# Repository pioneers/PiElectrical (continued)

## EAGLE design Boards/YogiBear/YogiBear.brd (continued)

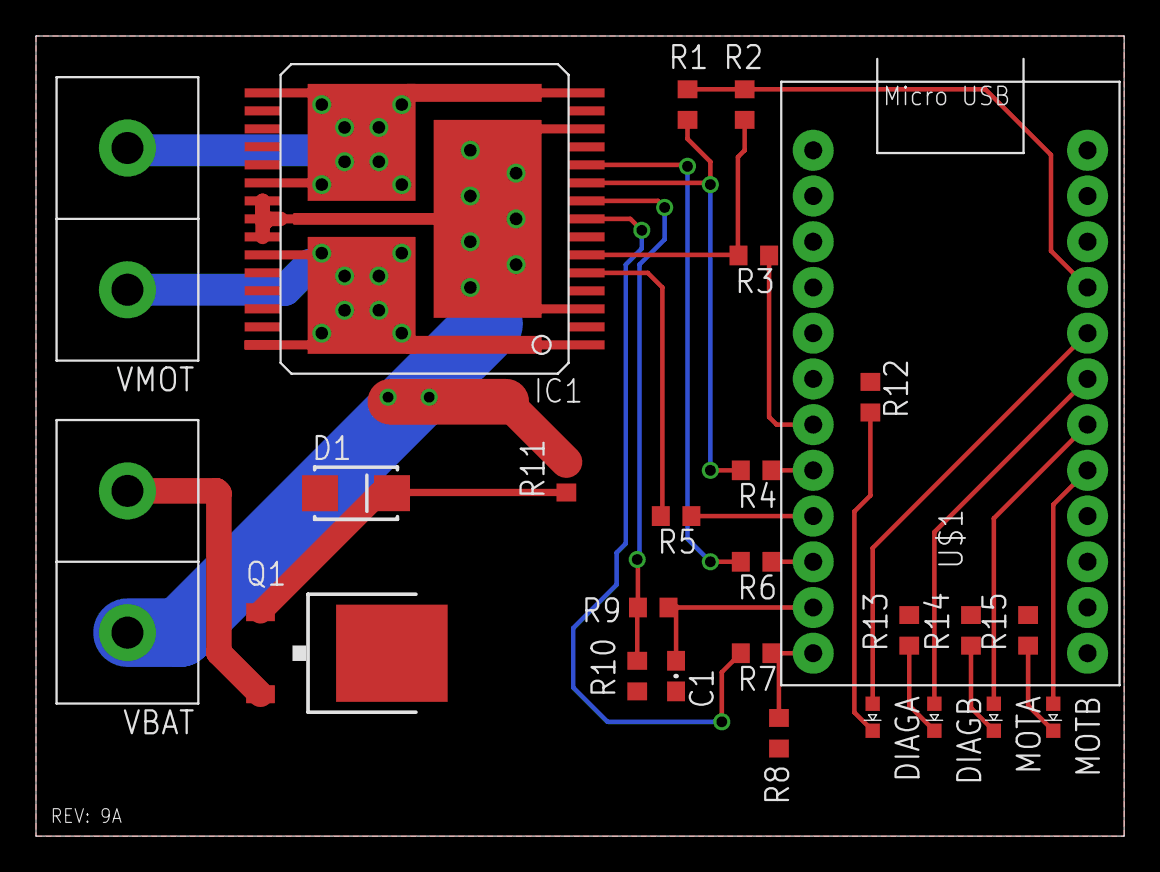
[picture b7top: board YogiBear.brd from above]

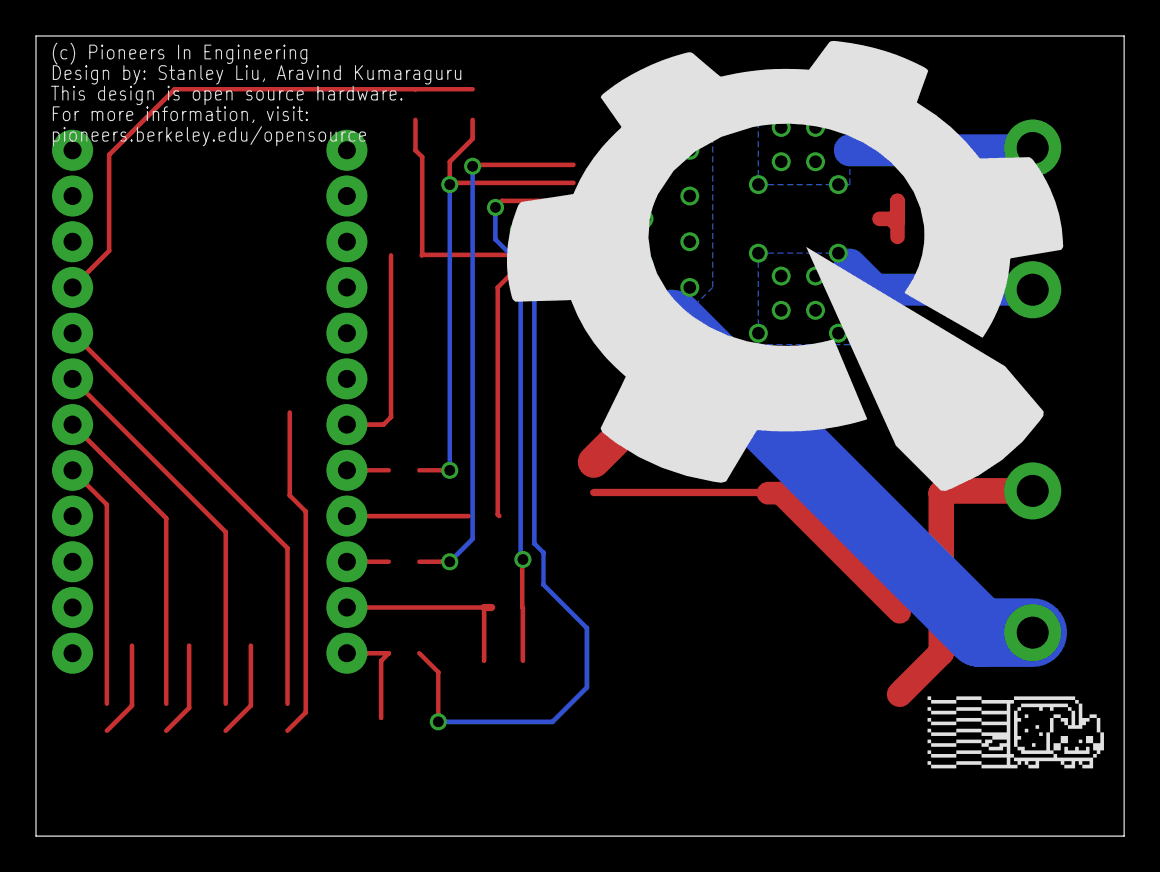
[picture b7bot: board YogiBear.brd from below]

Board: 2 copper layers, 60.5 x 44.5 mm, 28 parts (2 on the bottom side), 27 nets.

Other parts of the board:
U$2: PIE-LOGO
U$3: NYAN-1CM
